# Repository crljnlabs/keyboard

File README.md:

# keyboard

The crljn keypad: six keys, a rotary encoder with a push button and a 1.69 inch
display, on an ESP32-S3 Super Mini. This repository holds its firmware and its
circuit board.

Over USB the keypad is a vendor-defined HID device, so no operating system
treats it as a keyboard and nothing it sends ever types into a window. What a
key does is up to the program on the PC,
[anydeck](https://github.com/crljnlabs/anydeck), whose device contract
(`docs/device-protocol.md` there) this firmware keeps to.

- What the keypad says over USB, byte for byte: [docs/hid.md](docs/hid.md)

The firmware itself is short: `src/main.cpp` names the keypad's parts, and the
[anydeck library](https://github.com/crljnlabs/anydeck-library) does
everything between them and the PC. PlatformIO fetches it from GitHub.

## What the firmware does

- Reads the six keys and the encoder, and reports them to the PC.
- Tells the PC what it is made of, the display included.
- Plays anydeck's intro on the display at the start, then shows what the PC
  sends, put together from pieces.
- Shows a status screen of its own while the PC does not draw: the encoder's
  position and last direction, and which keys are held.
- Sleeps: the display after 5 minutes on its own screen, the whole keypad
  while the Mac sleeps; a key wakes the Mac if the Mac allows it.
- Logs over the same USB cable, as a serial port.

## Building and flashing

Needs Python 3 and PlatformIO (`pio`). Everything else - the toolchain, the
anydeck library, LovyanGFX, esptool - PlatformIO fetches itself on the first
build. Before every build the scripts fetch the anydeck library's newest
commit, and the build's `manifest.json` says which one went in.

Working on the library at the same time: clone it next to this repository and
link it instead, so every change there is in the next build here.

```bash
git clone https://github.com/crljnlabs/anydeck-library.git ../anydeck-library
```

```ini
lib_deps = symlink://../anydeck-library
```

```bash
python3 scripts/flash.py
```

The everyday command: compiles, flashes the board and opens the serial monitor.
It remembers the port that worked and only asks again when that one is gone.
`-p <port>` picks a port once, `--no-monitor` leaves the monitor closed.

```bash
python3 scripts/build.py
```

Compiles only, into `build/<timestamp>/`, which is not tracked.

```bash
python3 scripts/deploy.py
```

Publishes a build that already exists as a version, `release/<version>/`, which
is tracked. It never compiles, so the bytes that were tested are the bytes that
get published. It suggests the newest build and the next minor version.

```bash
python3 release/install.py
```

Flashes a published version, the newest unless one is named; `--list` shows
them. Nothing is published yet.

## Technology

- C++ with PlatformIO and the Arduino framework, for the ESP32-S3 Super Mini
  (module ESP32-S3FH4R2: 4 MB flash, 2 MB PSRAM). The platform is pioarduino's,
  pinned to Arduino core 3.3.12 (ESP-IDF 5.5.5), so a build is reproducible.
  PlatformIO's own platform ends at core 2.0.17, whose USB driver dropped the
  keypad off the bus while reports and display packets crossed;
  `platformio.ini` says more.
- USB through TinyUSB (`ARDUINO_USB_MODE=0`), which a vendor-defined HID
  interface needs; the serial port sits next to it on the same device.
- The display, an ST7789 panel, through the anydeck library and LovyanGFX;
  its panel, size and pins are in `src/main.cpp`.

## Where things are

| | |
|---|---|
| `src/main.cpp` | the firmware: which parts the keypad has, on which pins |
| `include/pins.h` | every GPIO the firmware touches, and why the pins do not match the schematic's net names |
| `platformio.ini` | the board and the USB setup |
| `docs/` | the USB protocol |
| `kicad/` | schematic, board, 3D model, gerbers and an interactive BOM |
| `scripts/` | building, flashing and publishing |
| `release/` | published versions, and the script that installs them |

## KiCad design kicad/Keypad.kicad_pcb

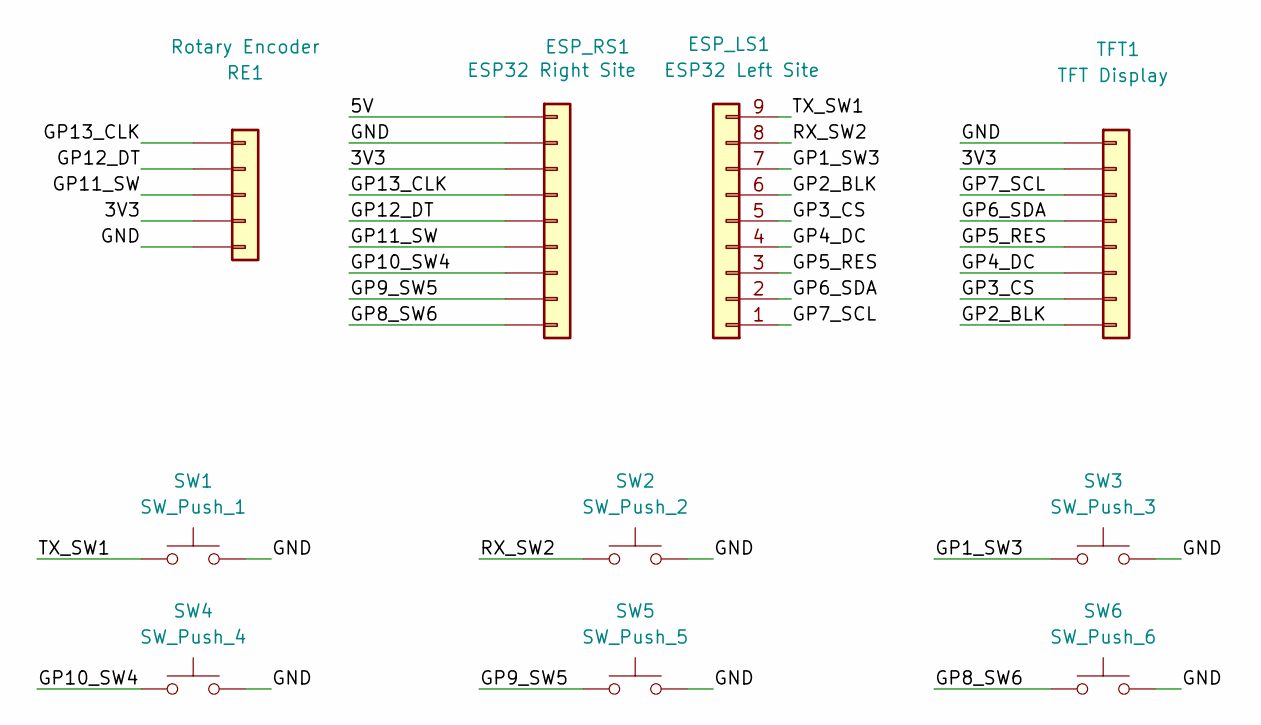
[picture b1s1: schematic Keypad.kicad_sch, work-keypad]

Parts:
ESP_LS1: ESP32 Left Site; PinSocket_1x09_P2.54mm_Vertical
ESP_RS1: ESP32 Right Site; PinSocket_1x09_P2.54mm_Vertical
RE1: Rotary Encoder; PinSocket_1x05_P2.54mm_Horizontal
SW1: SW_Push_1; SW_Hotswap_Kailh_MX_1.00u
SW2: SW_Push_2; SW_Hotswap_Kailh_MX_1.00u
SW3: SW_Push_3; SW_Hotswap_Kailh_MX_1.00u
SW4: SW_Push_4; SW_Hotswap_Kailh_MX_1.00u
SW5: SW_Push_5; SW_Hotswap_Kailh_MX_1.00u
SW6: SW_Push_6; SW_Hotswap_Kailh_MX_1.00u
TFT1: TFT Display; PinSocket_1x08_P2.54mm_Vertical

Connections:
/3V3: ESP_RS1.3, RE1.4, TFT1.2
/5V: ESP_RS1.1
/GND: ESP_RS1.2, RE1.5, SW1.1, SW2.1, SW3.1, SW4.1, SW5.1, SW6.1, TFT1.1
/GP1_SW3: ESP_LS1.7, SW3.2
/GP2_BLK: ESP_LS1.6, TFT1.8
/GP3_CS: ESP_LS1.5, TFT1.7
/GP4_DC: ESP_LS1.4, TFT1.6
/GP5_RES: ESP_LS1.3, TFT1.5
/GP6_SDA: ESP_LS1.2, TFT1.4
/GP7_SCL: ESP_LS1.1, TFT1.3
/GP8_SW6: ESP_RS1.9, SW6.2
/GP9_SW5: ESP_RS1.8, SW5.2
/GP10_SW4: ESP_RS1.7, SW4.2
/GP11_SW: ESP_RS1.6, RE1.3
/GP12_DT: ESP_RS1.5, RE1.2
/GP13_CLK: ESP_RS1.4, RE1.1
/RX_SW2: ESP_LS1.8, SW2.2
/TX_SW1: ESP_LS1.9, SW1.2

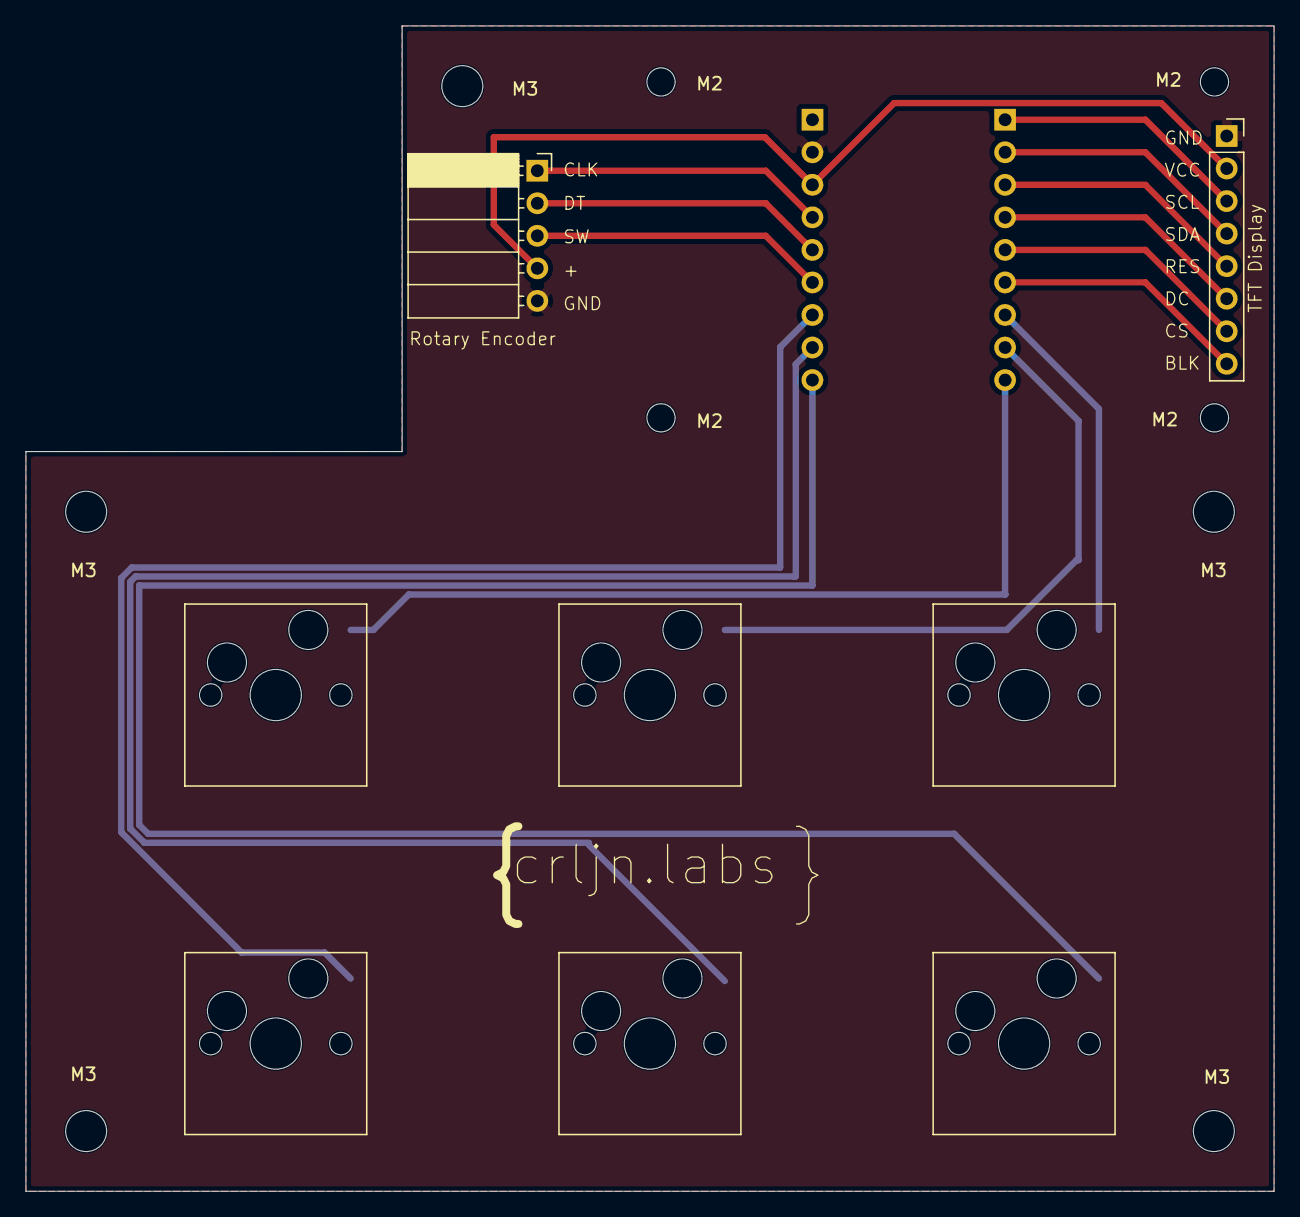
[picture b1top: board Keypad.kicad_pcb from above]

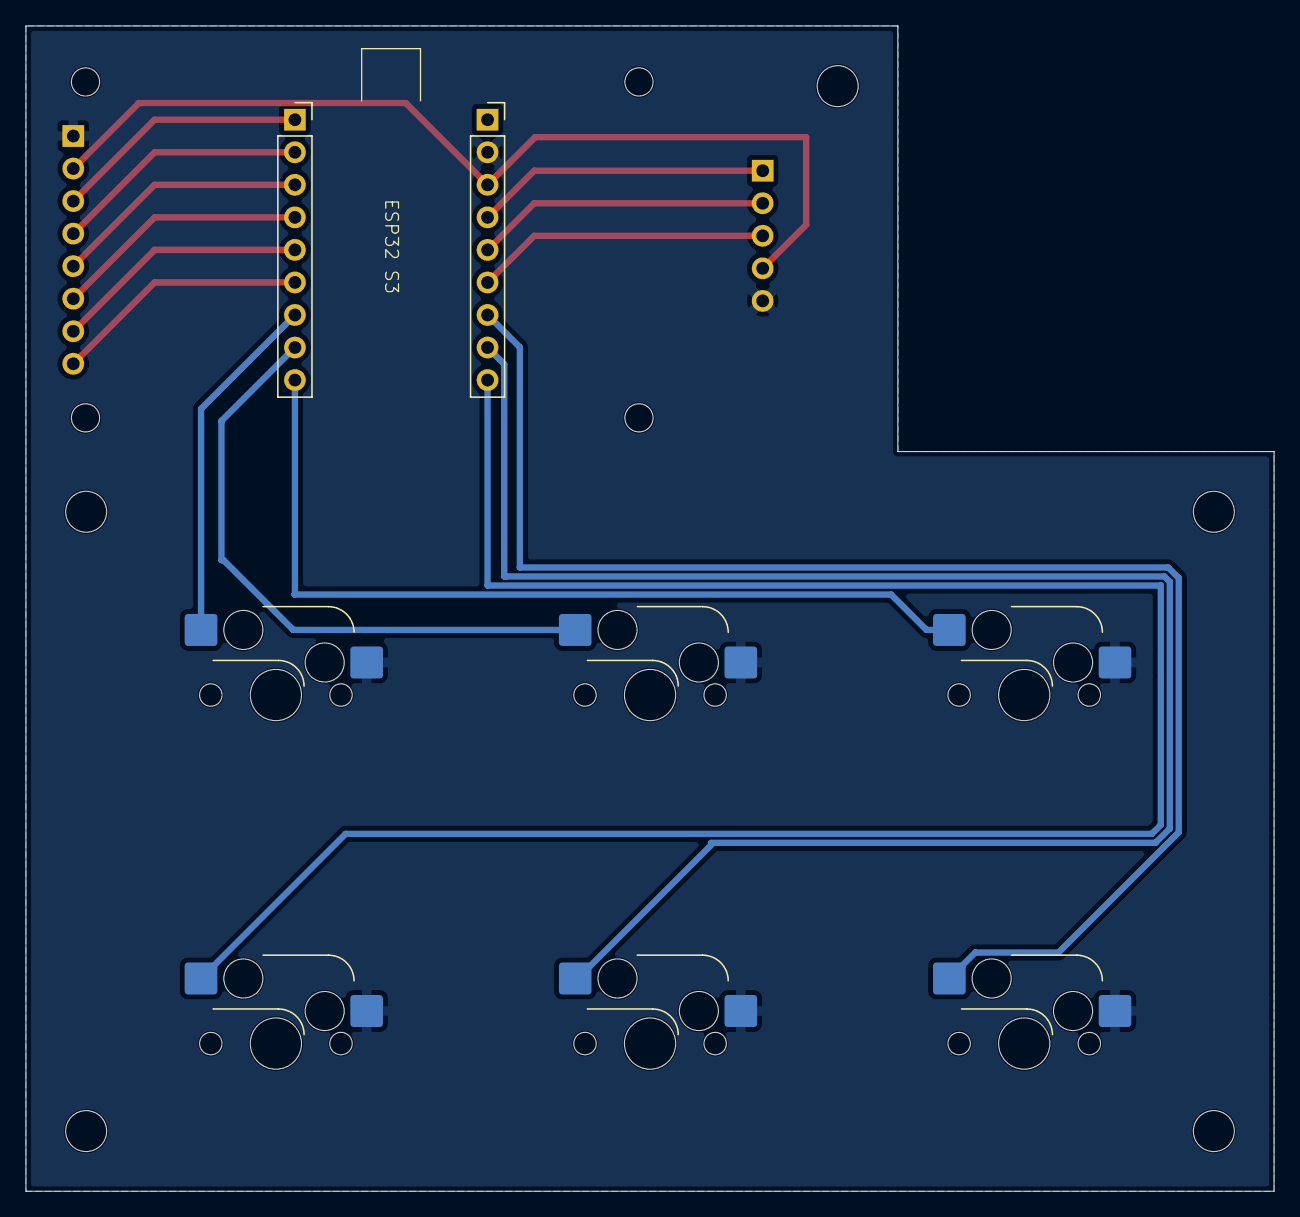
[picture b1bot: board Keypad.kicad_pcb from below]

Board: 2 copper layers, 97.4 x 91.0 mm, 10 parts (2 on the bottom side), 17 nets.
